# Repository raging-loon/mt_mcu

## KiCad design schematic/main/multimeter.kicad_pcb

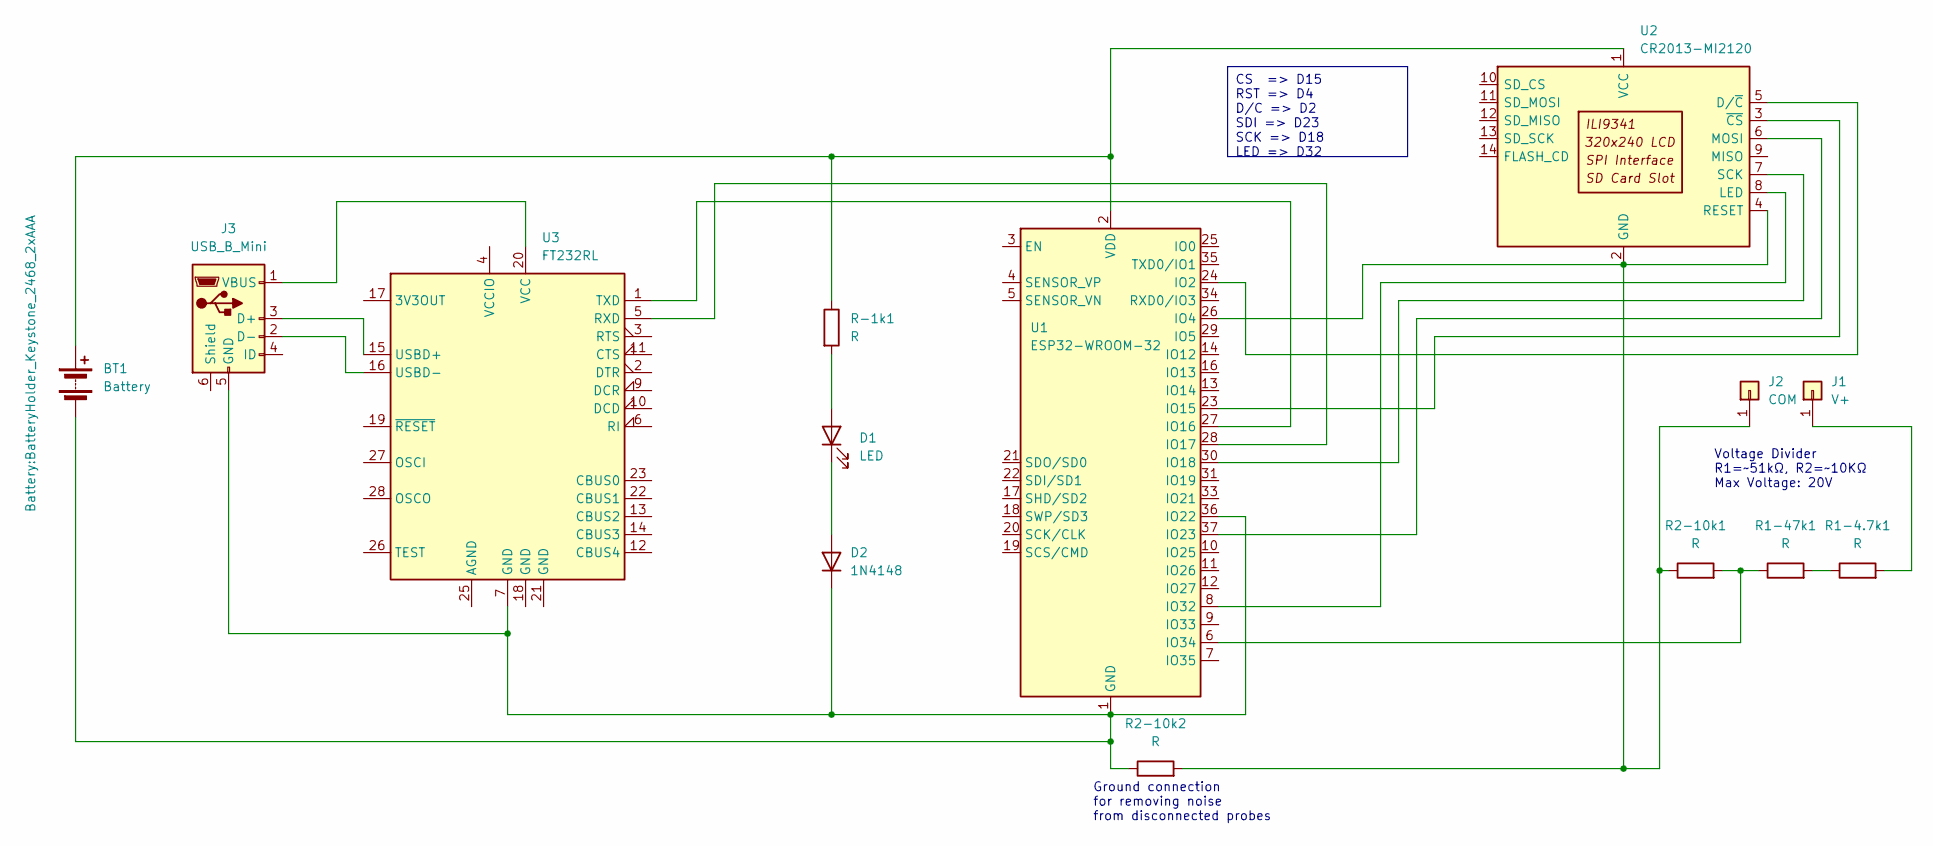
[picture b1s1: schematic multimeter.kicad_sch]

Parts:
BT1: Battery; BatteryHolder_Keystone_2468_2xAAA
D1: LED; LED_D3.0mm
D2: 1N4148; D_DO-35_SOD27_P7.62mm_Horizontal
J1: V+; TestPoint_Plated_Hole_D2.0mm
J2: COM; TestPoint_Plated_Hole_D2.0mm
J3: USB_B_Mini; USB_Mini-B_Wuerth_65100516121_Horizontal
R1-4.7k1, R1-47k1, R2-10k1, R2-10k2: R; R_1218_3246Metric
R-1k1: R; R_1218_3246Metric
U1: ESP32-WROOM-32
U2: CR2013-MI2120
U3: FT232RL; SSOP-28_5.3x10.2mm_P0.65mm

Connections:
unnamed: BT1.1 (+), R-1k1.1, U1.2 (VDD), U2.1 (VCC)
unnamed: BT1.2 (-), D2.1 (K), J3.5 (GND), R2-10k2.1, U1.1 (GND), U1.15 (GND), U1.36 (IO22), U1.38 (GND), U1.39 (GND), U3.7 (GND)
unnamed: D1.2 (A), R-1k1.2
unnamed: D1.1 (K), D2.2 (A)
unnamed: J1.1, R1-4.7k1.2
unnamed: J2.1, R2-10k1.1, R2-10k2.2, U1.26 (IO4), U2.2 (GND), U2.4 (RESET)
unnamed: J3.3 (D+), U3.15 (USBD+)
unnamed: J3.2 (D-), U3.16 (USBD-)
unnamed: J3.1 (VBUS), U3.20 (VCC)
unnamed: R1-4.7k1.1, R1-47k1.2
unnamed: U1.24 (IO2), U2.5 (D/~C)
unnamed: U1.23 (IO15), U2.3 (~CS)
unnamed: U1.27 (IO16), U3.1 (TXD)
unnamed: U1.28 (IO17), U3.5 (RXD)
unnamed: U1.30 (IO18), U2.7 (SCK)
unnamed: U1.37 (IO23), U2.6 (MOSI)
unnamed: U1.8 (IO32), U2.8 (LED)
unnamed: R1-47k1.1, R2-10k1.2, U1.6 (IO34)

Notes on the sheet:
CS => D15 RST => D4 D/C => D2 SDI => D23 SCK => D18 LED => D32
Voltage Divider R1=~51kΩ, R2=~10KΩ Max Voltage: 20V
Ground connection for removing noise from disconnected probes

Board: 2 copper layers, 14 parts (0 on the bottom side), 18 nets, no tracks yet.

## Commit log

2024-12-11 add lvgl + lvgl driver deps
2024-12-11 modified: .gitignore new file: CMakeLists.txt modified: README.md deleted: components/ESP32_TFT_library new file: components/lvgl new file: dependencies.lock new file: main/CMakeLists.txt new file: m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
2024-12-11 purge lvgl
2024-12-11 add base voltage reader
2024-12-12 added USB detection + voltage reading
2024-12-12 adding mtcp documentation + if flags
2024-12-12 added ISR removal to mtcp destructor
2024-12-12 added schematics
2024-12-12 added basic voltage reader task
2024-12-14 [unstable] Added MTCP watcher + USB detection
2024-12-18 Fixed plug/unplug bug + consolidate MTCP files
2024-12-19 moved task code. reversed greeting process
2024-12-19 added sdkconfig + kconfig
